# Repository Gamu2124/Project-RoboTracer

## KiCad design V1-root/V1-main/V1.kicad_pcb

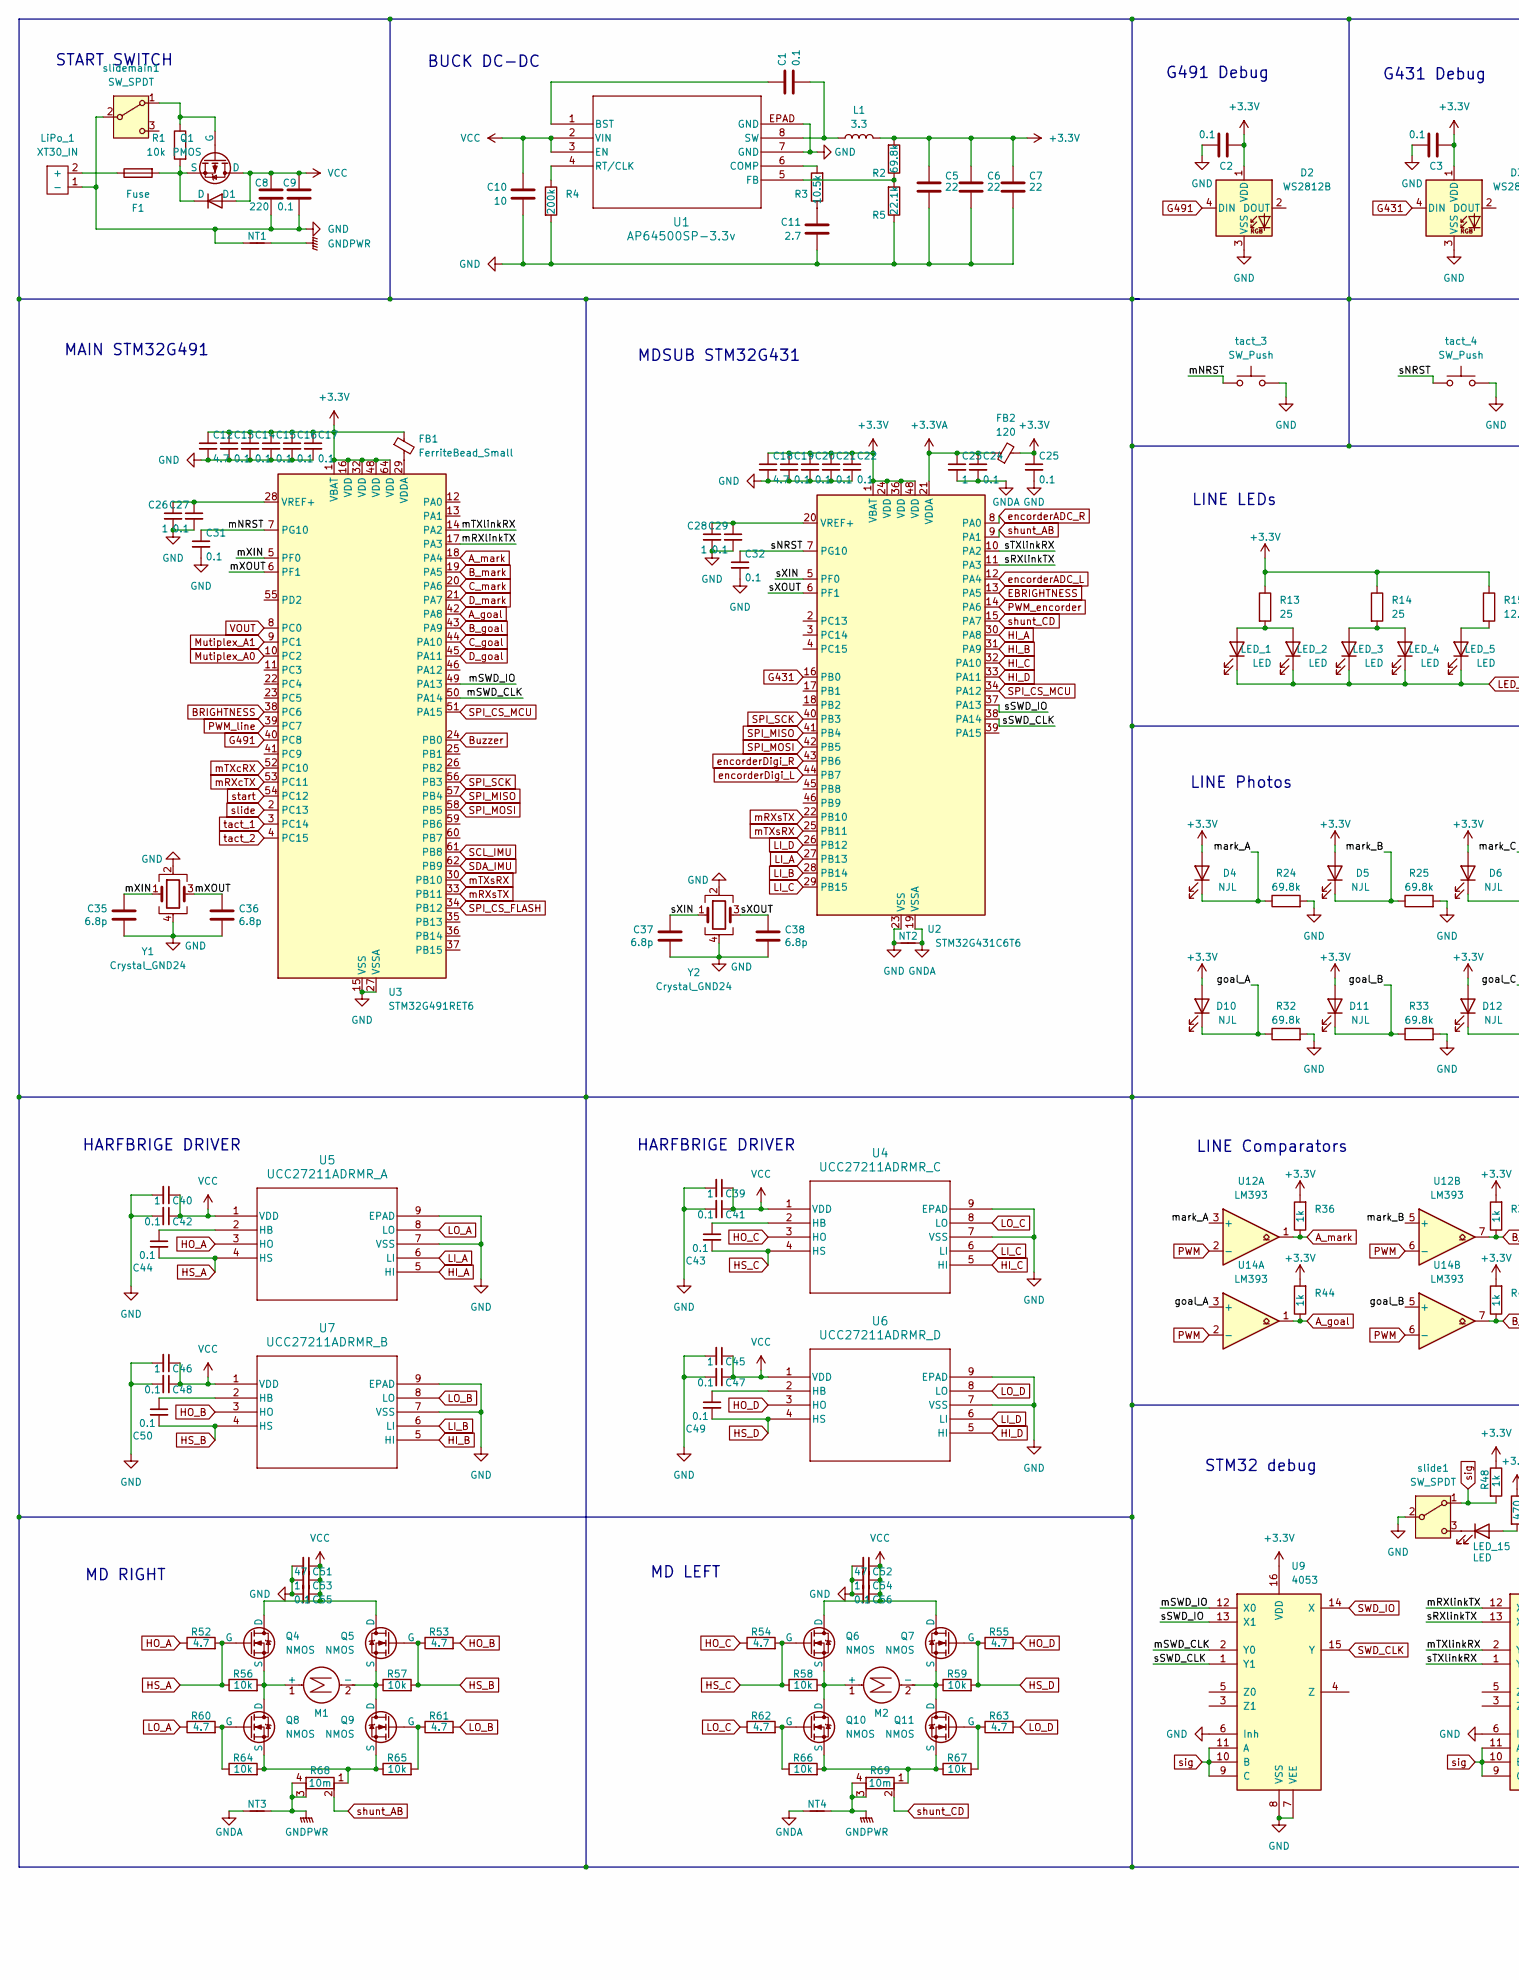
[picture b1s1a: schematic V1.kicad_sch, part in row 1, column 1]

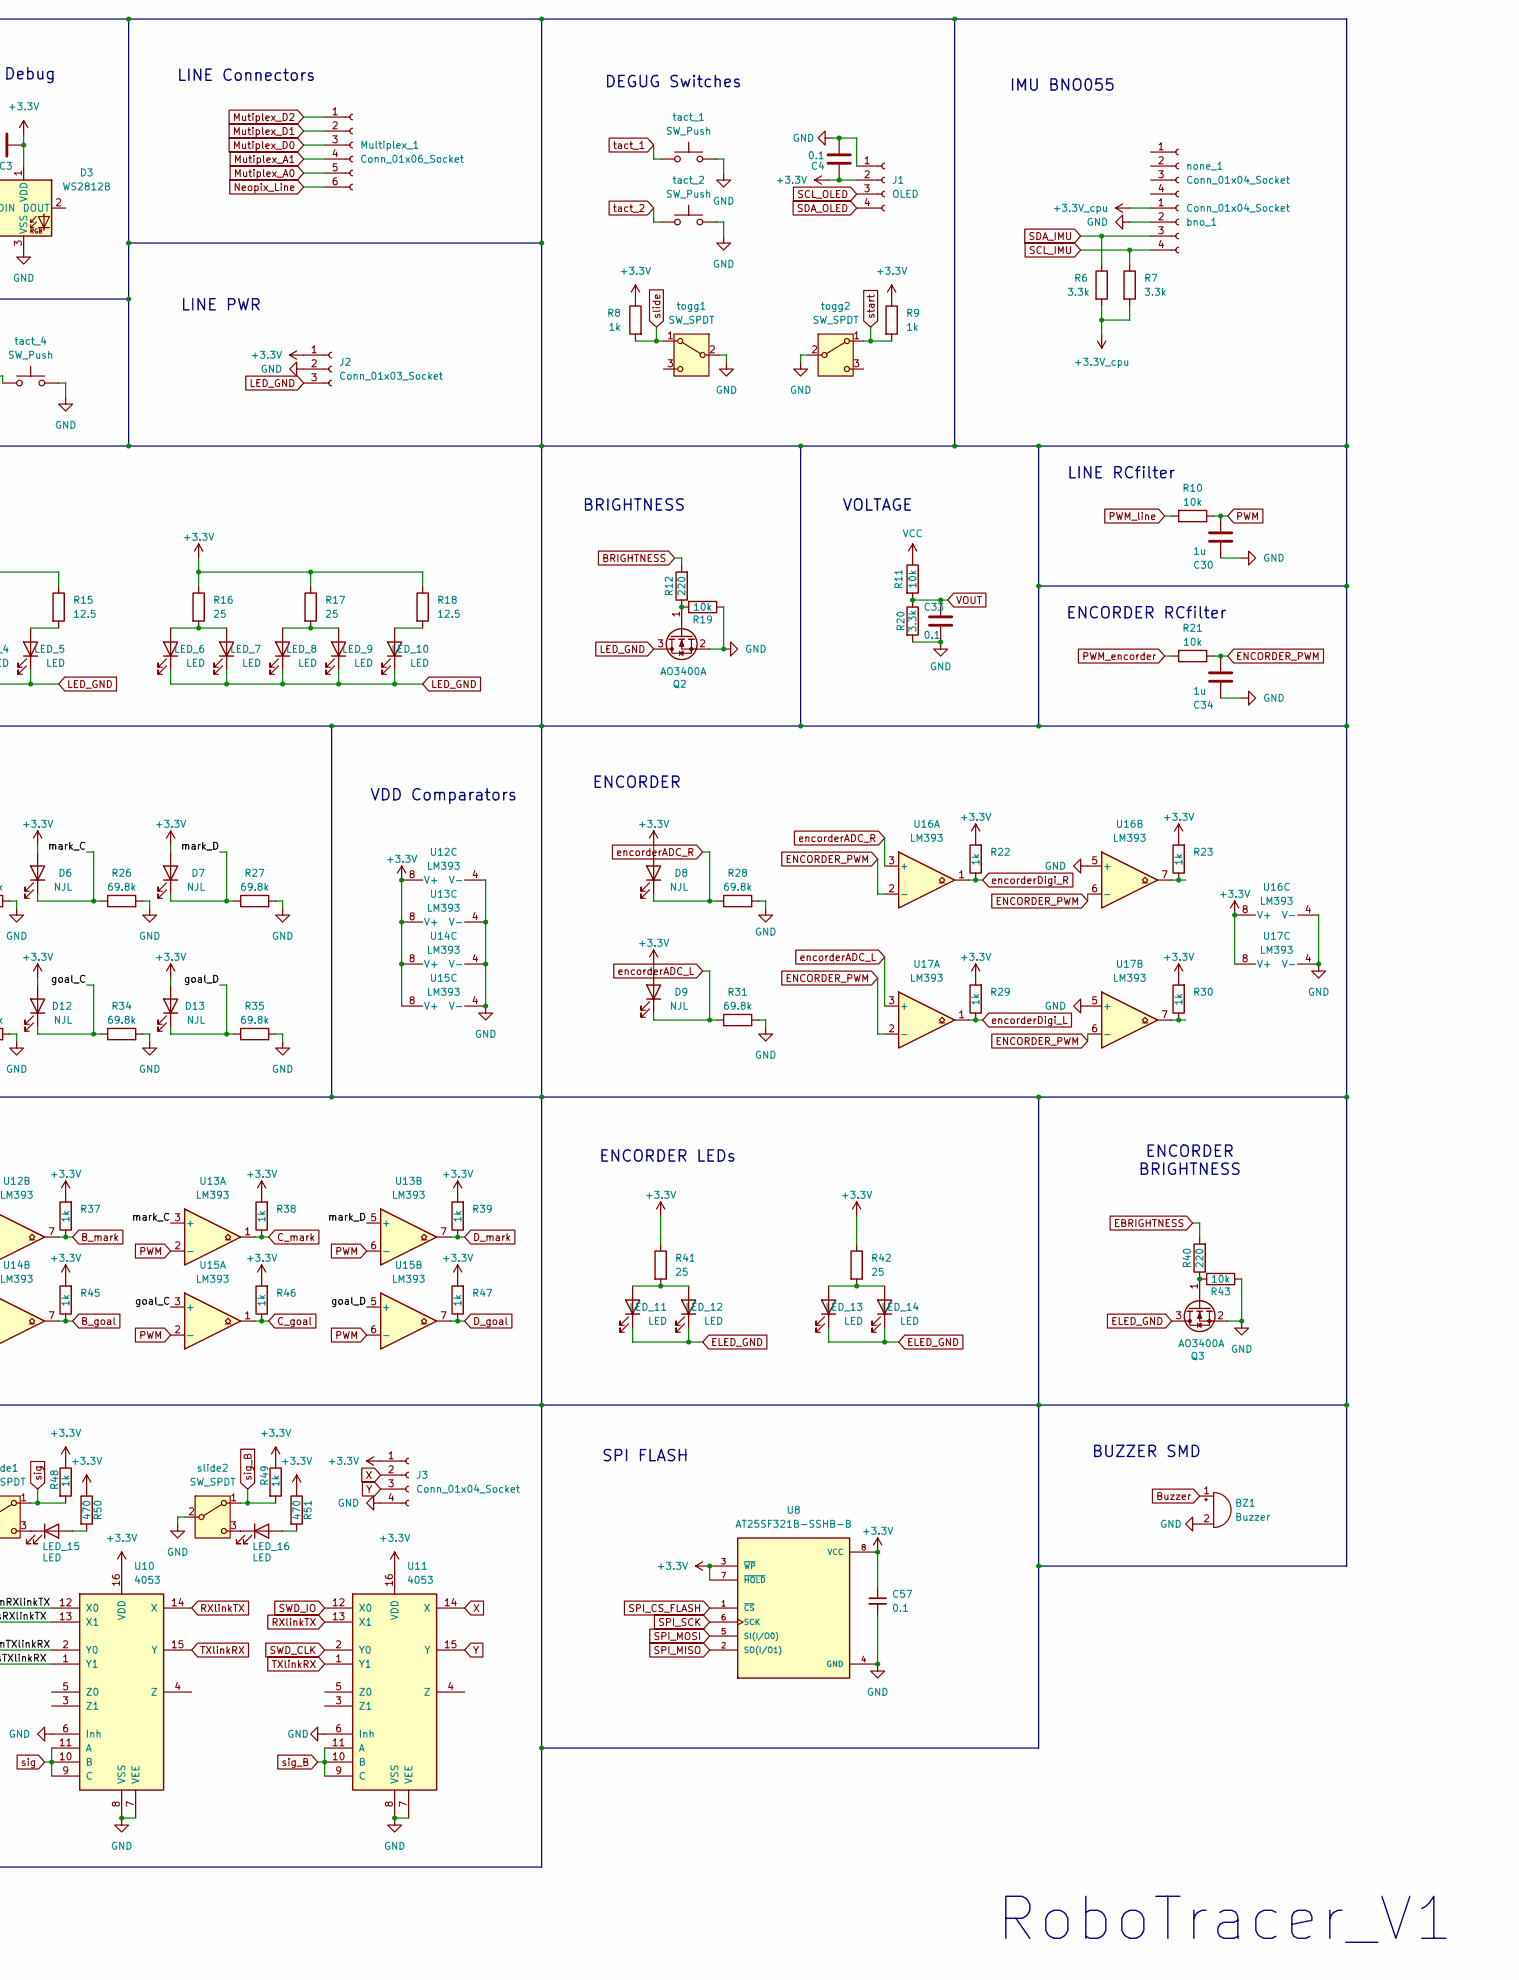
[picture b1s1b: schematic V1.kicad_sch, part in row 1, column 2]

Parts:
BZ1: Buzzer; Buzzer_Murata_PKLCS1212E
C1, C13, C14, C15, C16, C17, C19, C20, C21, C22, C24, C25, C27, C29, C31, C32, C33, C41, C42, C43, C44, C47, C48, C49, C50, C55, C56, C57: 0.1; C_0603_1608Metric_Pad1.08x0.95mm_HandSolder
C2, C3: 0.1; C_0603_1608Metric_Pad1.08x0.95mm_HandSolder; LCSC C1848
C4: 0.1; C_0603_1608Metric_Pad1.08x0.95mm_HandSolder; LCSC C1581
C5: 22; C_0805_2012Metric; LCSC C2887274
C6, C7: 22; C_0805_2012Metric
C8: 220; C_0402_1005Metric; LCSC C1548
C9: 0.1; C_0603_1608Metric_Pad1.08x0.95mm_HandSolder; LCSC C1548
C10: 10; C_0603_1608Metric_Pad1.08x0.95mm_HandSolder; LCSC C2992602
C11: 2.7; C_1206_3216Metric
C12, C18: 4.7; C_0805_2012Metric_Pad1.18x1.45mm_HandSolder
C23, C26, C28, C39, C40, C45, C46, C53, C54: 1; C_0805_2012Metric_Pad1.18x1.45mm_HandSolder
C30, C34: 1u; C_0805_2012Metric_Pad1.18x1.45mm_HandSolder; LCSC C3348
C35, C36, C37, C38: 6.8p; C_0402_1005Metric; LCSC C1548
C51, C52: 47; CP_Elec_6.3x5.9
D1: D; D_SOD-123F
D2, D3: WS2812B; LED_WS2812B_PLCC4_5.0x5.0mm_P3.2mm
D4, D5, D6, D7, D8, D9, D10, D11, D12, D13: NJL; LED_0603_1608Metric_Pad1.05x0.95mm_HandSolder
F1: Fuse; Fuseholder_Clip-5x20mm_Keystone_3517_Inline_P23.11x6.76mm_D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
FB1: FerriteBead_Small; R_0603_1608Metric_Pad0.98x0.95mm_HandSolder
FB2: 120; R_0603_1608Metric_Pad0.98x0.95mm_HandSolder
J1: OLED; PinSocket_1x04_P2.54mm_Vertical
J2: Conn_01x03_Socket; JST_XH_S3B-XH-A_1x03_P2.50mm_Horizontal
J3: Conn_01x04_Socket; PinSocket_1x04_P2.54mm_Vertical
L1: 3.3; L_Bourns_SRP7028A_7.3x6.6mm
LED_1, LED_2, LED_3, LED_4, LED_5, LED_6, LED_7, LED_8, LED_9, LED_10, LED_11, LED_12, LED_13, LED_14, LED_15, LED_16: LED; LED_0603_1608Metric_Pad1.05x0.95mm_HandSolder
LiPo_1: XT30_IN; AMASS_XT30U-M_1x02_P5.0mm_Vertical
M1, M2: Motor_DC; PinHeader_1x02_P2.54mm_Vertical
Multiplex_1: Conn_01x06_Socket; TE_84952-6_1x06-1MP_P1.0mm_Horizontal
NT1, NT2, NT3, NT4: NetTie_2; NetTie-2_THT_Pad1.0mm
Q1: PMOS; TO-252-2
Q2, Q3: AO3400A; SOT-23
Q4, Q5, Q6, Q7, Q8, Q9, Q10, Q11: NMOS; LFPAK56
R1, R19, R43: 10k; R_0603_1608Metric
R2: 69.8k; R_0805_2012Metric; LCSC C17803
R3: 10.5k; R_0402_1005Metric; LCSC C25850
R4: 200k; R_0805_2012Metric; LCSC C17539
R5: 22.1k; R_0805_2012Metric
R6: 3.3k; R_Axial_DIN0207_L6.3mm_D2.5mm_P10.16mm_Horizontal
R7: 3.3k; R_Axial_DIN0207_L6.3mm_D2.5mm_P10.16mm_Horizontal; LCSC C22978
R8, R9, R48, R49: 1k; R_Axial_DIN0207_L6.3mm_D2.5mm_P10.16mm_Horizontal
R10, R21: 10k; R_0603_1608Metric; LCSC C23098
R11: 10k; R_Axial_DIN0207_L6.3mm_D2.5mm_P10.16mm_Horizontal; LCSC C26033
R12, R40: 220; R_0805_2012Metric
R13, R14, R16, R17, R41, R42: 25; R_0603_1608Metric
R15, R18: 12.5; R_0603_1608Metric
R20: 3.3k; R_Axial_DIN0207_L6.3mm_D2.5mm_P10.16mm_Horizontal; LCSC C26033
R22, R23, R29, R30, R36, R37, R38, R39, R44, R45, R46, R47: 1k; R_0603_1608Metric; LCSC C23098
R24, R25, R26, R27, R28, R31, R32, R33, R34, R35: 69.8k; R_0603_1608Metric; LCSC C23098
R50, R51: 470; R_0603_1608Metric
R52, R53, R54, R55, R60, R61, R62, R63: 4.7; R_0603_1608Metric_Pad0.98x0.95mm_HandSolder
R56, R57, R58, R59, R64, R65, R66, R67: 10k; R_0603_1608Metric_Pad0.98x0.95mm_HandSolder
R68, R69: 10m; FC4L110_OHM
U1: AP64500SP-3.3v; SO-8EP_DIO
U2: STM32G431C6T6; LQFP-48_7x7mm_P0.5mm
U3: STM32G491RET6; LQFP-64_10x10mm_P0.5mm
U4: UCC27211ADRMR_C; DRM8_3P38X2P45_TEX
U5: UCC27211ADRMR_A; DRM8_3P38X2P45_TEX
U6: UCC27211ADRMR_D; DRM8_3P38X2P45_TEX
U7: UCC27211ADRMR_B; DRM8_3P38X2P45_TEX
U8: AT25SF321B-SSHB-B; SOIC127P599X175-8N; PARTREV G
U9, U10, U11: 4053; SOT403-1_NXP
U12, U13, U14, U15, U16, U17: LM393; SOIC-8_3.9x4.9mm_P1.27mm
Y1, Y2: Crystal_GND24; XTAL4P_ABM8W_ABR; LCSC C20625731
bno_1: Conn_01x04_Socket; PinSocket_1x04_P2.54mm_Vertical
none_1: Conn_01x04_Socket; PinSocket_1x04_P2.54mm_Vertical
slide1, slide2: SW_SPDT; SLIDE_akiduki
slidemain1: SW_SPDT; SLIDE_akiduki
tact_1, tact_2: SW_Push; SW_TH_Tactile_Omron_B3F-10xx
tact_3, tact_4: SW_Push; Switch_SKRPABE010
togg1, togg2: SW_SPDT; SLIDE_akiduki

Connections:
+3.3V: C2.2, C3.2, C4.1, C5.1, C6.1, C7.1, C12.1, C13.1, C14.1, C15.1, C16.1, C17.1, C18.1, C19.1, C20.1, C21.1, C22.1, C25.1, C57.1, D2.1 (VDD), D3.1 (VDD), D4.2 (A), D5.2 (A), D6.2 (A), D7.2 (A), D8.2 (A), D9.2 (A), D10.2 (A), D11.2 (A), D12.2 (A), D13.2 (A), FB1.1, FB2.2, J1.2, J2.1, J3.1, L1.2, R2.2, R8.1, R9.1, R13.1, R14.1, R15.1, R16.1, R17.1, R18.1, R22.2, R23.2, R29.2, R30.2, R36.2, R37.2, R38.2, R39.2, R41.1, R42.1, R44.2, R45.2, R46.2, R47.2, R48.1, R49.1, R50.1, R51.1, U2.1 (VBAT), U2.24 (VDD), U2.36 (VDD), U2.48 (VDD), U3.1 (VBAT), U3.16 (VDD), U3.32 (VDD), U3.48 (VDD), U3.64 (VDD), U8.3 (~WP), U8.7 (~HOLD), U8.8 (VCC), U9.16 (VDD), U10.16 (VDD), U11.16 (VDD), U12.8 (V+), U13.8 (V+), U14.8 (V+), U15.8 (V+), U16.8 (V+), U17.8 (V+)
+3.3VA: C23.1, C24.1, FB2.1, U2.21 (VDDA)
+3.3V_cpu: R6.2, R7.2, bno_1.1
/goal_A: D10.1 (K), R32.1, U14.3 (+)
/goal_B: D11.1 (K), R33.1, U14.5 (+)
/goal_C: D12.1 (K), R34.1, U15.3 (+)
/goal_D: D13.1 (K), R35.1, U15.5 (+)
/mNRST: C31.1, U3.7 (PG10), tact_3.1
/mRXlinkTX: U3.17 (PA3), U10.12 (X0)
/mSWD_CLK: U3.50 (PA14), U9.2 (Y0)
/mSWD_IO: U3.49 (PA13), U9.12 (X0)
/mTXlinkRX: U3.14 (PA2), U10.2 (Y0)
/mXIN: C35.1, U3.5 (PF0), Y1.1
/mXOUT: C36.1, U3.6 (PF1), Y1.3
/mark_A: D4.1 (K), R24.1, U12.3 (+)
/mark_B: D5.1 (K), R25.1, U12.5 (+)
/mark_C: D6.1 (K), R26.1, U13.3 (+)
/mark_D: D7.1 (K), R27.1, U13.5 (+)
/sNRST: C32.1, U2.7 (PG10), tact_4.1
/sRXlinkTX: U2.11 (PA3), U10.13 (X1)
/sSWD_CLK: U2.38 (PA14), U9.1 (Y1)
/sSWD_IO: U2.37 (PA13), U9.13 (X1)
/sTXlinkRX: U2.10 (PA2), U10.1 (Y1)
/sXIN: C37.1, U2.5 (PF0), Y2.1
/sXOUT: C38.1, U2.6 (PF1), Y2.3
A_goal: R44.1, U3.42 (PA8), U14.1
A_mark: R36.1, U3.18 (PA4), U12.1
BRIGHTNESS: R12.2, U3.38 (PC6)
B_goal: R45.1, U3.43 (PA9), U14.7
B_mark: R37.1, U3.19 (PA5), U12.7
Buzzer: BZ1.1 (+), U3.24 (PB0)
C_goal: R46.1, U3.44 (PA10), U15.1
C_mark: R38.1, U3.20 (PA6), U13.1
D_goal: R47.1, U3.45 (PA11), U15.7
D_mark: R39.1, U3.21 (PA7), U13.7
EBRIGHTNESS: R40.2, U2.13 (PA5)
ELED_GND: LED_11.1 (K), LED_12.1 (K), LED_13.1 (K), LED_14.1 (K), Q3.3 (D)
ENCORDER_PWM: C34.1, R21.2, U16.2 (-), U16.6 (-), U17.2 (-), U17.6 (-)
G431: D3.4 (DIN), U2.16 (PB0)
G491: D2.4 (DIN), U3.40 (PC8)
GND: BZ1.2 (-), C2.1, C3.1, C4.2, C5.2, C6.2, C7.2, C8.2, C9.2, C10.2, C11.2, C12.2, C13.2, C14.2, C15.2, C16.2, C17.2, C18.2, C19.2, C20.2, C21.2, C22.2, C25.2, C26.2, C27.2, C28.2, C29.2, C30.2, C31.2, C32.2, C33.2, C34.2, C35.2, C36.2, C37.2, C38.2, C39.2, C40.2, C41.2, C42.2, C45.2, C46.2, C47.2, C48.2, C51.2, C52.2, C53.2, C54.2, C55.2, C56.2, C57.2, D2.3 (VSS), D3.3 (VSS), J1.1, J2.2, J3.4, LiPo_1.1 (-), NT1.1, NT2.1, Q2.2 (S), Q3.2 (S), R4.2, R5.1, R19.1, R20.2, R24.2, R25.2, R26.2, R27.2, R28.2, R31.2, R32.2, R33.2, R34.2, R35.2, R43.1, U1.7 (GND), U1.EPAD (GND), U2.23 (VSS), U2.35 (VSS), U2.47 (VSS), U3.15 (VSS), U3.27 (VSSA), U3.31 (VSS), U3.47 (VSS), U3.63 (VSS), U4.7 (VSS), U4.9 (EPAD), U5.7 (VSS), U5.9 (EPAD), U6.7 (VSS), U6.9 (EPAD), U7.7 (VSS), U7.9 (EPAD), U8.4 (GND), U9.6 (Inh), U9.7 (VEE), U9.8 (VSS), U10.6 (Inh), U10.7 (VEE), U10.8 (VSS), U11.6 (Inh), U11.7 (VEE), U11.8 (VSS), U12.4 (V-), U13.4 (V-), U14.4 (V-), U15.4 (V-), U16.4 (V-), U16.5 (+), U17.4 (V-), U17.5 (+), Y1.2, Y1.4, Y2.2, Y2.4, bno_1.2, slide1.2 (B), slide2.2 (B), slidemain1.2 (B), tact_1.2, tact_2.2, tact_3.2, tact_4.2, togg1.2 (B), togg2.2 (B); also elsewhere on the board
GNDA: C23.2, C24.2, NT2.2, NT3.2, NT4.2, U2.19 (VSSA)
GNDPWR: NT1.2, NT3.1, NT4.1, R68.3, R68.4, R69.3, R69.4
HI_A: U2.30 (PA8), U5.5 (HI)
HI_B: U2.31 (PA9), U7.5 (HI)
HI_C: U2.32 (PA10), U4.5 (HI)
HI_D: U2.33 (PA11), U6.5 (HI)
HO_A: R52.1, U5.3 (HO)
HO_B: R53.2, U7.3 (HO)
HO_C: R54.1, U4.3 (HO)
HO_D: R55.2, U6.3 (HO)
HS_A: C44.2, Q4.2 (G), R52.2, R56.1, U5.4 (HS)
HS_B: C50.2, Q5.2 (G), R53.1, R57.2, U7.4 (HS)
HS_C: C43.2, Q6.2 (G), R54.2, R58.1, U4.4 (HS)
HS_D: C49.2, Q7.2 (G), R55.1, R59.2, U6.4 (HS)
LED_GND: J2.3, LED_1.1 (K), LED_2.1 (K), LED_3.1 (K), LED_4.1 (K), LED_5.1 (K), LED_6.1 (K), LED_7.1 (K), LED_8.1 (K), LED_9.1 (K), LED_10.1 (K), Q2.3 (D)
LI_A: U2.27 (PB13), U5.6 (LI)
LI_B: U2.28 (PB14), U7.6 (LI)
LI_C: U2.29 (PB15), U4.6 (LI)
LI_D: U2.26 (PB12), U6.6 (LI)
LO_A: R60.1, U5.8 (LO)
LO_B: R61.2, U7.8 (LO)
LO_C: R62.1, U4.8 (LO)
LO_D: R63.2, U6.8 (LO)
Mutiplex_A0: Multiplex_1.5, U3.10 (PC2)
Mutiplex_A1: Multiplex_1.4, U3.9 (PC1)
Mutiplex_D0: Multiplex_1.3
Mutiplex_D1: Multiplex_1.2
Mutiplex_D2: Multiplex_1.1
Neopix_Line: Multiplex_1.6
unnamed: C11.1, R3.1
unnamed: D1.1 (K), F1.2, Q1.3 (S), R1.2
unnamed: LED_1.2 (A), LED_2.2 (A), R13.2
unnamed: LED_3.2 (A), LED_4.2 (A), R14.2
unnamed: LED_5.2 (A), R15.2
unnamed: LED_6.2 (A), LED_7.2 (A), R16.2
unnamed: LED_8.2 (A), LED_9.2 (A), R17.2
unnamed: LED_10.2 (A), R18.2
unnamed: LED_11.2 (A), LED_12.2 (A), R41.2
unnamed: LED_13.2 (A), LED_14.2 (A), R42.2
unnamed: LED_15.2 (A), R50.2
unnamed: LED_15.1 (K), slide1.3 (C)
unnamed: LED_16.2 (A), R51.2
unnamed: LED_16.1 (K), slide2.3 (C)
unnamed: F1.1, LiPo_1.2 (+)
unnamed: M1.1 (+), Q4.3 (S), Q8.1 (D), R56.2
unnamed: M1.2 (-), Q5.3 (S), Q9.1 (D), R57.1
unnamed: M2.1 (+), Q6.3 (S), Q10.1 (D), R58.2
unnamed: M2.2 (-), Q7.3 (S), Q11.1 (D), R59.1
unnamed 89: Q1.1 (G), R1.1, slidemain1.1 (A); also elsewhere on the board
unnamed: Q2.1 (G), R12.1, R19.2
unnamed: Q3.1 (G), R40.1, R43.2
unnamed: Q8.2 (G), R60.2, R64.1
unnamed: Q8.3 (S), Q9.3 (S), R64.2, R65.1, R68.1
unnamed: Q9.2 (G), R61.1, R65.2
unnamed: Q10.2 (G), R62.2, R66.1
unnamed: Q10.3 (S), Q11.3 (S), R66.2, R67.1, R69.1
unnamed: Q11.2 (G), R63.1, R67.2
unnamed: R23.1, U16.7
unnamed: R30.1, U17.7
unnamed: C1.1, U1.1 (BST)
unnamed: R3.2, U1.6 (COMP)
unnamed: R2.1, R5.2, U1.5 (FB)
unnamed: R4.1, U1.4 (RT/CLK)
unnamed: C1.2, L1.1, U1.8 (SW)
unnamed: C28.1, C29.1, U2.20 (VREF+)
unnamed: FB1.2, U3.29 (VDDA)
unnamed: C26.1, C27.1, U3.28 (VREF+)
unnamed: C43.1, U4.2 (HB)
unnamed: C44.1, U5.2 (HB)
unnamed: C49.1, U6.2 (HB)
unnamed: C50.1, U7.2 (HB)
PWM: C30.1, R10.2, U12.2 (-), U12.6 (-), U13.2 (-), U13.6 (-), U14.2 (-), U14.6 (-), U15.2 (-), U15.6 (-)
PWM_encorder: R21.1, U2.14 (PA6)
PWM_line: R10.1, U3.39 (PC7)
RXlinkTX: U10.14 (X), U11.13 (X1)
SCL_IMU: R7.1, U3.61 (PB8), bno_1.4
SCL_OLED: J1.3
SDA_IMU: R6.1, U3.62 (PB9), bno_1.3
SDA_OLED: J1.4
SPI_CS_FLASH: U3.34 (PB12), U8.1 (~CS)
SPI_CS_MCU: U2.34 (PA12), U3.51 (PA15)
SPI_MISO: U2.41 (PB4), U3.57 (PB4), U8.2 (SO(I/O1))
SPI_MOSI: U2.42 (PB5), U3.58 (PB5), U8.5 (SI(I/O0))
SPI_SCK: U2.40 (PB3), U3.56 (PB3), U8.6 (SCK)
SWD_CLK: U9.15 (Y), U11.2 (Y0)
SWD_IO: U9.14 (X), U11.12 (X0)
TXlinkRX: U10.15 (Y), U11.1 (Y1)
VCC: C8.1, C9.1, C10.1, C39.1, C40.1, C41.1, C42.1, C45.1, C46.1, C47.1, C48.1, C51.1, C52.1, C53.1, C54.1, C55.1, C56.1, D1.2 (A), Q1.2 (D), Q4.1 (D), Q5.1 (D), Q6.1 (D), Q7.1 (D), R11.1, U1.2 (VIN), U1.3 (EN), U4.1 (VDD), U5.1 (VDD), U6.1 (VDD), U7.1 (VDD)
VOUT: C33.1, R11.2, R20.1, U3.8 (PC0)
X: J3.2, U11.14 (X)
Y: J3.3, U11.15 (Y)
encorderADC_L: D9.1 (K), R31.1, U2.12 (PA4), U17.3 (+)
encorderADC_R: D8.1 (K), R28.1, U2.8 (PA0), U16.3 (+)
encorderDigi_L: R29.1, U2.44 (PB7), U17.1
encorderDigi_R: R22.1, U2.43 (PB6), U16.1
mRXcTX: U3.53 (PC11)
mRXsTX: U2.22 (PB10), U3.33 (PB11)
mTXcRX: U3.52 (PC10)
mTXsRX: U2.25 (PB11), U3.30 (PB10)
shunt_AB: R68.2, U2.9 (PA1)
shunt_CD: R69.2, U2.15 (PA7)
sig: R48.2, U9.9 (C), U9.10 (B), U9.11 (A), U10.9 (C), U10.10 (B), U10.11 (A), slide1.1 (A)
sig_B: R49.2, U11.9 (C), U11.10 (B), U11.11 (A), slide2.1 (A)
slide: R8.2, U3.2 (PC13), togg1.1 (A)
start: R9.2, U3.54 (PC12), togg2.1 (A)
tact_1: U3.3 (PC14), tact_1.1
tact_2: U3.4 (PC15), tact_2.1

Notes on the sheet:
ENCORDER RCfilter
BUZZER SMD
MD RIGHT
HARFBRIGE DRIVER
ENCORDER BRIGHTNESS
MDSUB STM32G431
DEGUG Switches
BUCK DC-DC
ENCORDER LEDs
SPI FLASH
LINE RCfilter
STM32 debug
MD LEFT
RoboTracer_V1
BRIGHTNESS
MAIN STM32G491
ENCORDER
LINE LEDs
G491 Debug
LINE Connectors
G431 Debug
LINE Photos
IMU BNO055
LINE PWR
START SWITCH
LINE Comparators
VDD Comparators
VOLTAGE

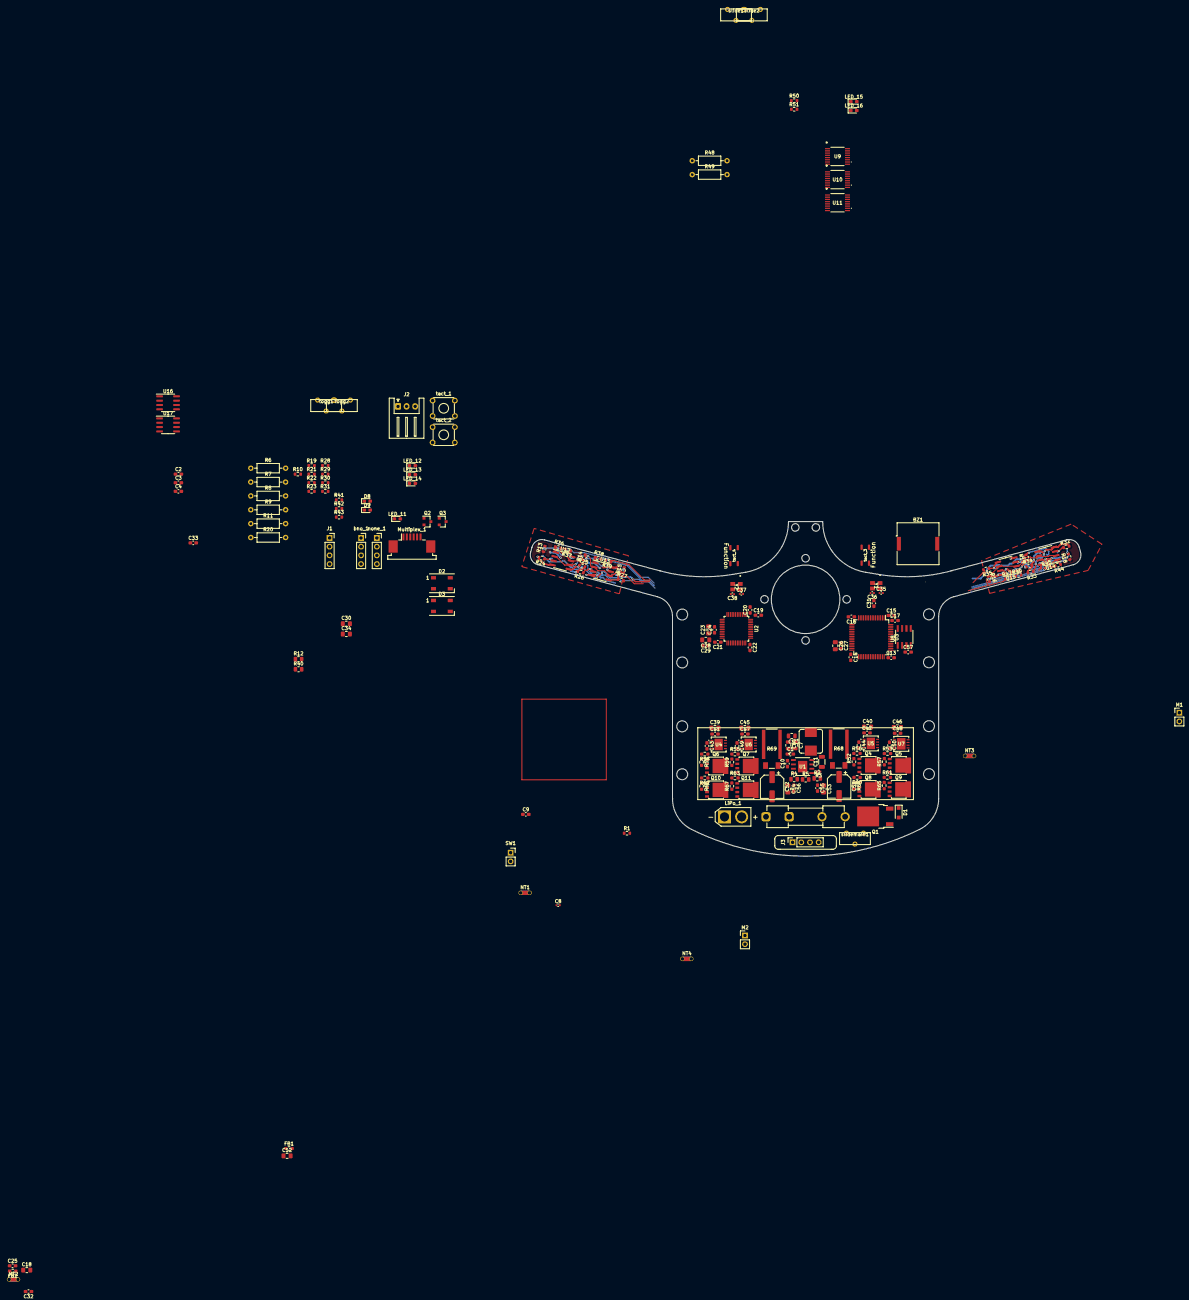
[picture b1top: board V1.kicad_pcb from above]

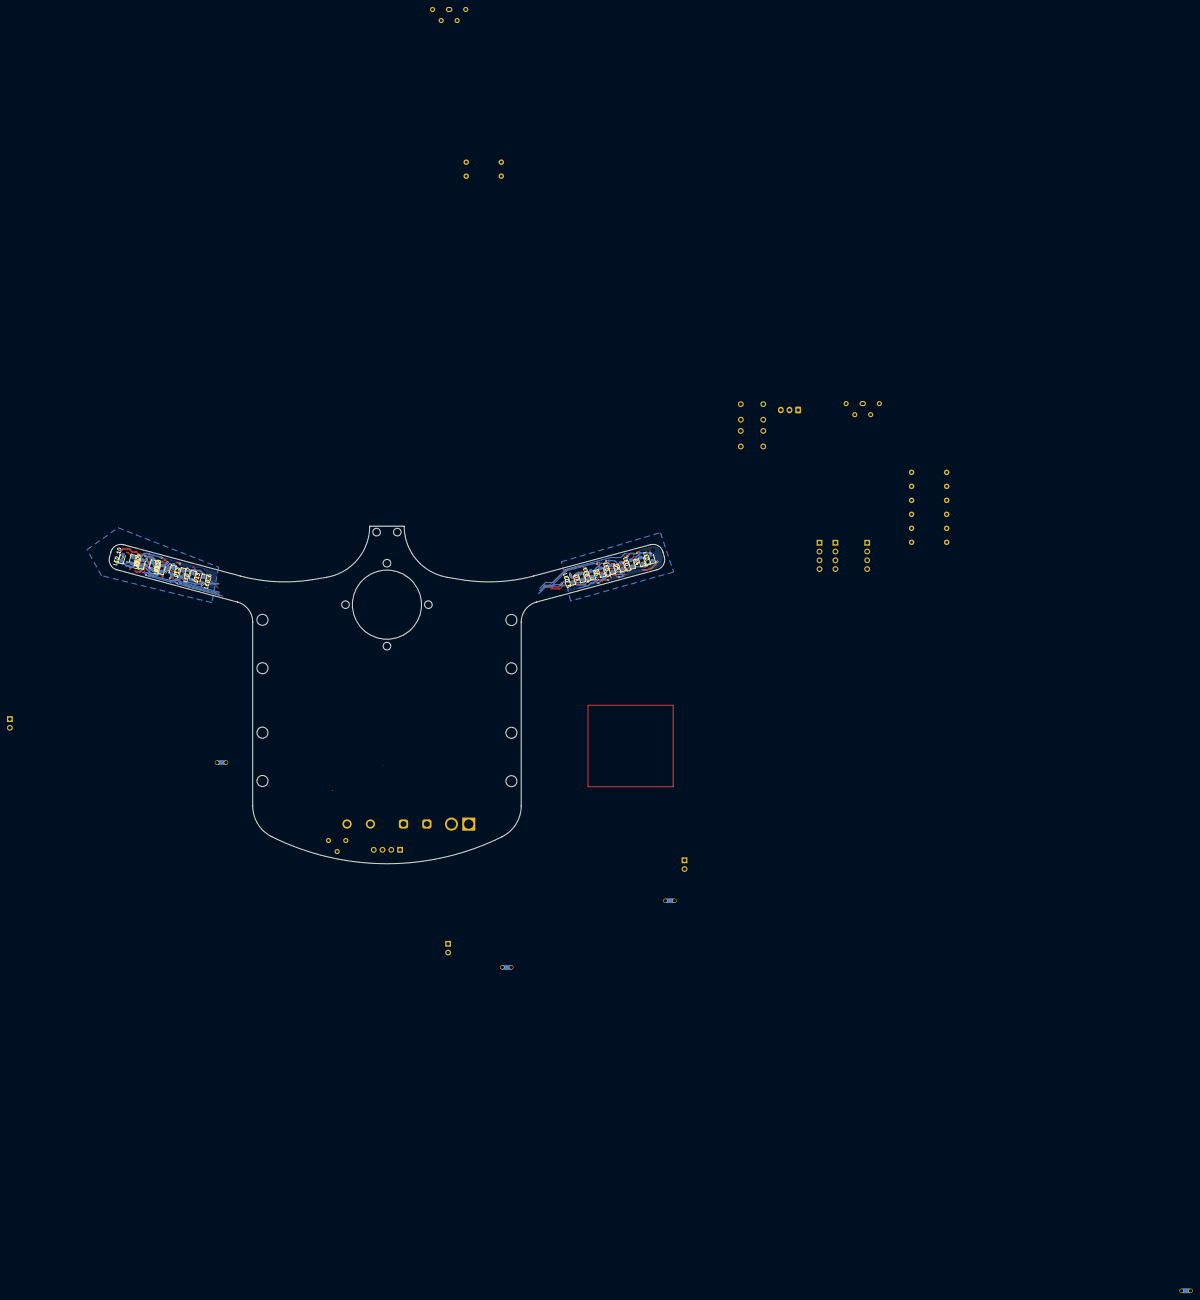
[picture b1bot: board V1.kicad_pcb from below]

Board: 2 copper layers, 160.8 x 97.7 mm, 213 parts (18 on the bottom side), 139 nets.

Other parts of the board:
SW1: SW_SPST; PinSocket_1x02_P2.54mm_Vertical

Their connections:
GND: SW1.1 (A); also elsewhere on the board
unnamed 89: SW1.2 (B); also elsewhere on the board
